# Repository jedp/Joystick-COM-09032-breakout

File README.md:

# Joystick COM-09032 Breakout Board

Breakout board for the COM-09032 Joystick.

Includes a footprint for the component which is surprisingly hard to come by.
The datasheet from Sparkfun includes no measurements of any use, which is a
tragedy, and the footprints I've found online do not quite match the physical
measurements I've taken on a real device.

Not the world's most beautiful footprint, but serviceable.

## BOM

- U1: Joystick COM-09032
- J1: Connector 2.54mm
- R1, R2: Resistor 0603 1k (or whatever you like, but they must be populated)
- H1, H2, H3, H4: Mounting hole 3.2mm M3

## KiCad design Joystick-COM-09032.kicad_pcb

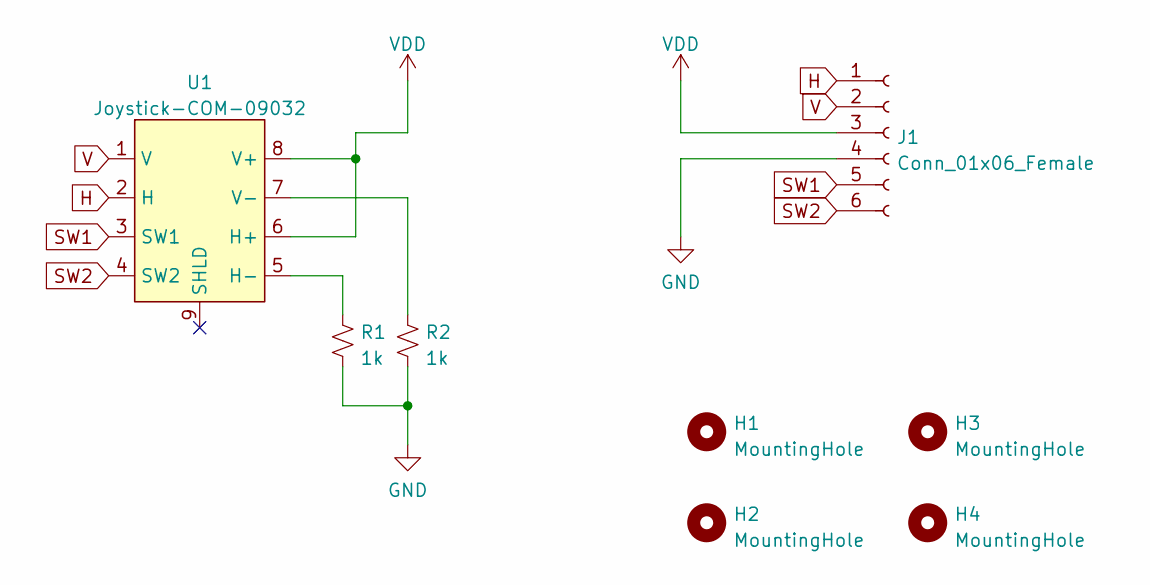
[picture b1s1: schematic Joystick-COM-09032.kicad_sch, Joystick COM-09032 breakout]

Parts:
H1, H2, H3, H4: MountingHole; MountingHole_3.2mm_M3
J1: Conn_01x06_Female; PinHeader_1x06_P2.54mm_Vertical
R1, R2: 1k; R_0603_1608Metric
U1: Joystick-COM-09032

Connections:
GND: J1.4, R1.2, R2.2
H: J1.1, U1.2 (H)
unnamed: R1.1, U1.5 (H-)
unnamed: R2.1, U1.7 (V-)
SW1: J1.5, U1.3 (SW1)
SW2: J1.6, U1.4 (SW2)
V: J1.2, U1.1 (V)
VDD: J1.3, U1.6 (H+), U1.8 (V+)

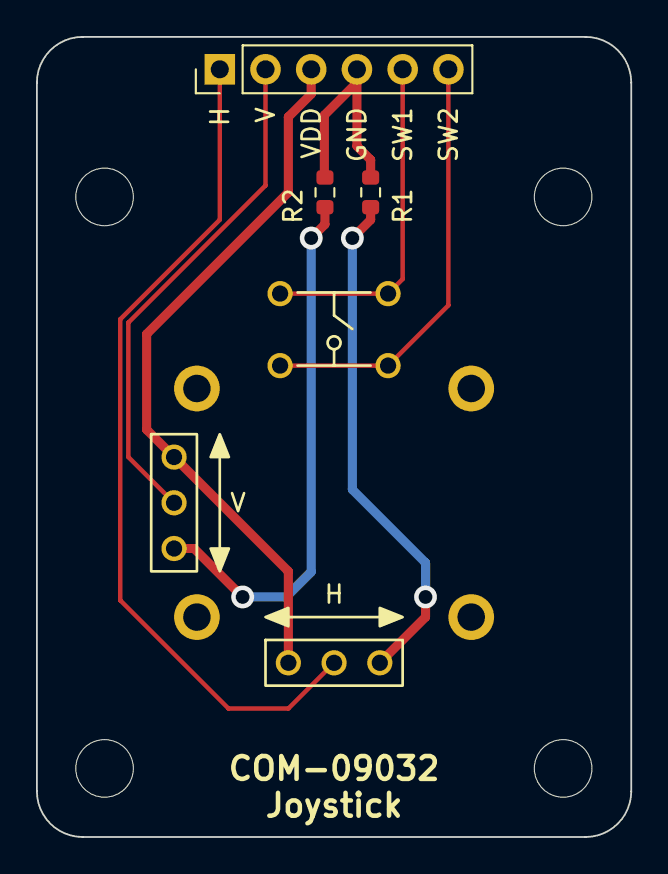
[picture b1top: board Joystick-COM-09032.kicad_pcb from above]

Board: 2 copper layers, 33.0 x 44.5 mm, 8 parts (0 on the bottom side), 8 nets.

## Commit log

2023-04-16 Component footprint and breakout board
2023-04-16 Add image of footprint
